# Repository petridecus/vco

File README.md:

6 Voice VCO, designed for Eurorack

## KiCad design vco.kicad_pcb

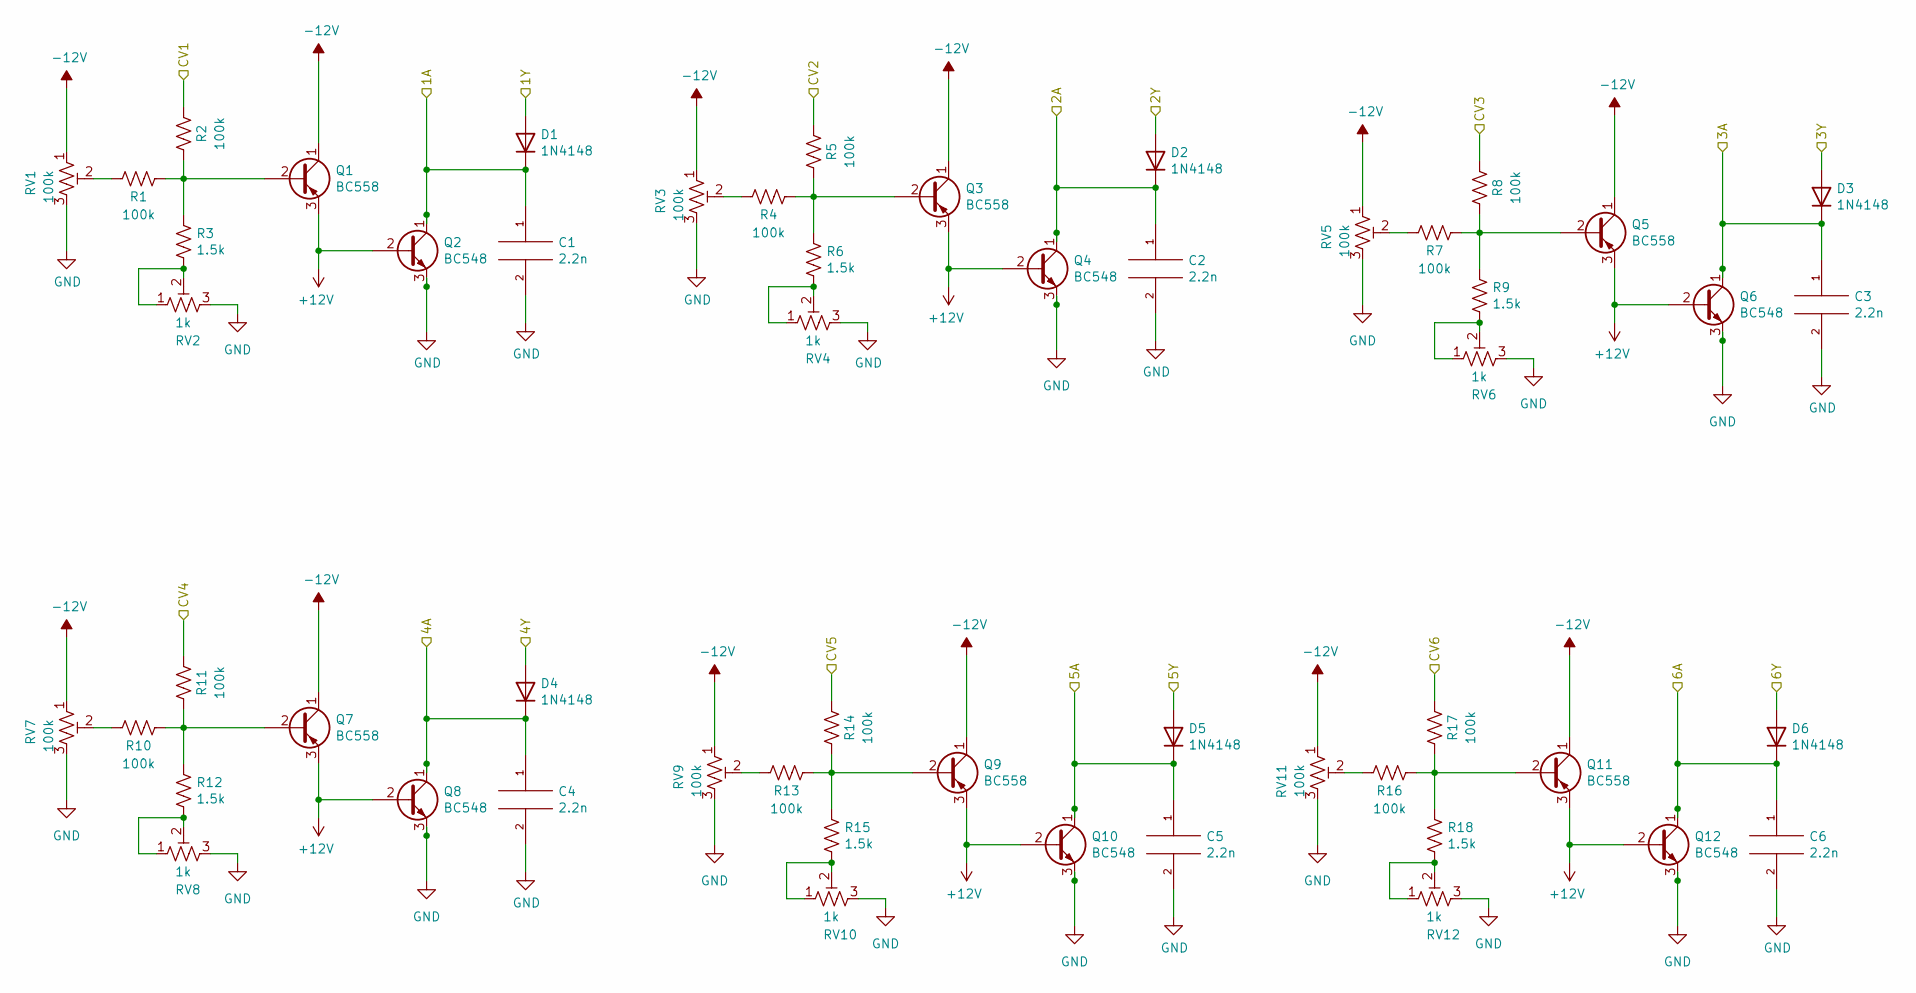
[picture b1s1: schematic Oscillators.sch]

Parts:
C1, C2, C3, C4, C5, C6: 2.2n; C_0603_1608Metric_Pad1.08x0.95mm_HandSolder
D1, D2, D3, D4, D5, D6: 1N4148; D_0603_1608Metric
Q1, Q3, Q5, Q7, Q9, Q11: BC558; SC-59_Handsoldering
Q2, Q4, Q6, Q8, Q10, Q12: BC548; SOT-23_Handsoldering
R1, R2, R4, R5, R7, R8, R10, R11, R13, R14, R16, R17: 100k; R_0603_1608Metric
R3, R6, R9, R12, R15, R18: 1.5k; R_0603_1608Metric
RV1, RV3, RV5, RV7, RV9, RV11: 100k; TRIM_3314J-1-104E
RV2, RV4, RV6, RV8, RV10, RV12: 1k; TRIM_3314J-1-104E

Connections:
+12V: Q1.3 (E), Q2.2 (B), Q3.3 (E), Q4.2 (B), Q5.3 (E), Q6.2 (B), Q7.3 (E), Q8.2 (B), Q9.3 (E), Q10.2 (B), Q11.3 (E), Q12.2 (B); also elsewhere on the board
-12V: Q1.1 (C), Q3.1 (C), Q5.1 (C), Q7.1 (C), Q9.1 (C), Q11.1 (C), RV1.1, RV3.1, RV5.1, RV7.1, RV9.1, RV11.1; also elsewhere on the board
/Sheet614BBE23/1A: C1.1, D1.1 (K), Q2.1 (C); also elsewhere on the board
/Sheet614BBE23/1Y: D1.2 (A); also elsewhere on the board
/Sheet614BBE23/2A: C2.1, D2.1 (K), Q4.1 (C); also elsewhere on the board
/Sheet614BBE23/2Y: D2.2 (A); also elsewhere on the board
/Sheet614BBE23/3A: C3.1, D3.1 (K), Q6.1 (C); also elsewhere on the board
/Sheet614BBE23/3Y: D3.2 (A); also elsewhere on the board
/Sheet614BBE23/4A: C4.1, D4.1 (K), Q8.1 (C); also elsewhere on the board
/Sheet614BBE23/4Y: D4.2 (A); also elsewhere on the board
/Sheet614BBE23/5A: C5.1, D5.1 (K), Q10.1 (C); also elsewhere on the board
/Sheet614BBE23/5Y: D5.2 (A); also elsewhere on the board
/Sheet614BBE23/6A: C6.1, D6.1 (K), Q12.1 (C); also elsewhere on the board
/Sheet614BBE23/6Y: D6.2 (A); also elsewhere on the board
CV1: R2.1; also elsewhere on the board
CV2: R5.1; also elsewhere on the board
CV3: R8.1; also elsewhere on the board
CV4: R11.1; also elsewhere on the board
CV5: R14.1; also elsewhere on the board
CV6: R17.1; also elsewhere on the board
GND: C1.2, C2.2, C3.2, C4.2, C5.2, C6.2, Q2.3 (E), Q4.3 (E), Q6.3 (E), Q8.3 (E), Q10.3 (E), Q12.3 (E), RV1.3, RV2.3, RV3.3, RV4.3, RV5.3, RV6.3, RV7.3, RV8.3, RV9.3, RV10.3, RV11.3, RV12.3; also elsewhere on the board
unnamed: Q1.2 (B), R1.1, R2.2, R3.1
unnamed: Q3.2 (B), R4.1, R5.2, R6.1
unnamed: Q5.2 (B), R7.1, R8.2, R9.1
unnamed: Q7.2 (B), R10.1, R11.2, R12.1
unnamed: Q9.2 (B), R13.1, R14.2, R15.1
unnamed: Q11.2 (B), R16.1, R17.2, R18.1
unnamed: R1.2, RV1.2
unnamed: R3.2, RV2.1, RV2.2
unnamed: R4.2, RV3.2
unnamed: R6.2, RV4.1, RV4.2
unnamed: R7.2, RV5.2
unnamed: R9.2, RV6.1, RV6.2
unnamed: R10.2, RV7.2
unnamed: R12.2, RV8.1, RV8.2
unnamed: R13.2, RV9.2
unnamed: R15.2, RV10.1, RV10.2
unnamed: R16.2, RV11.2
unnamed: R18.2, RV12.1, RV12.2

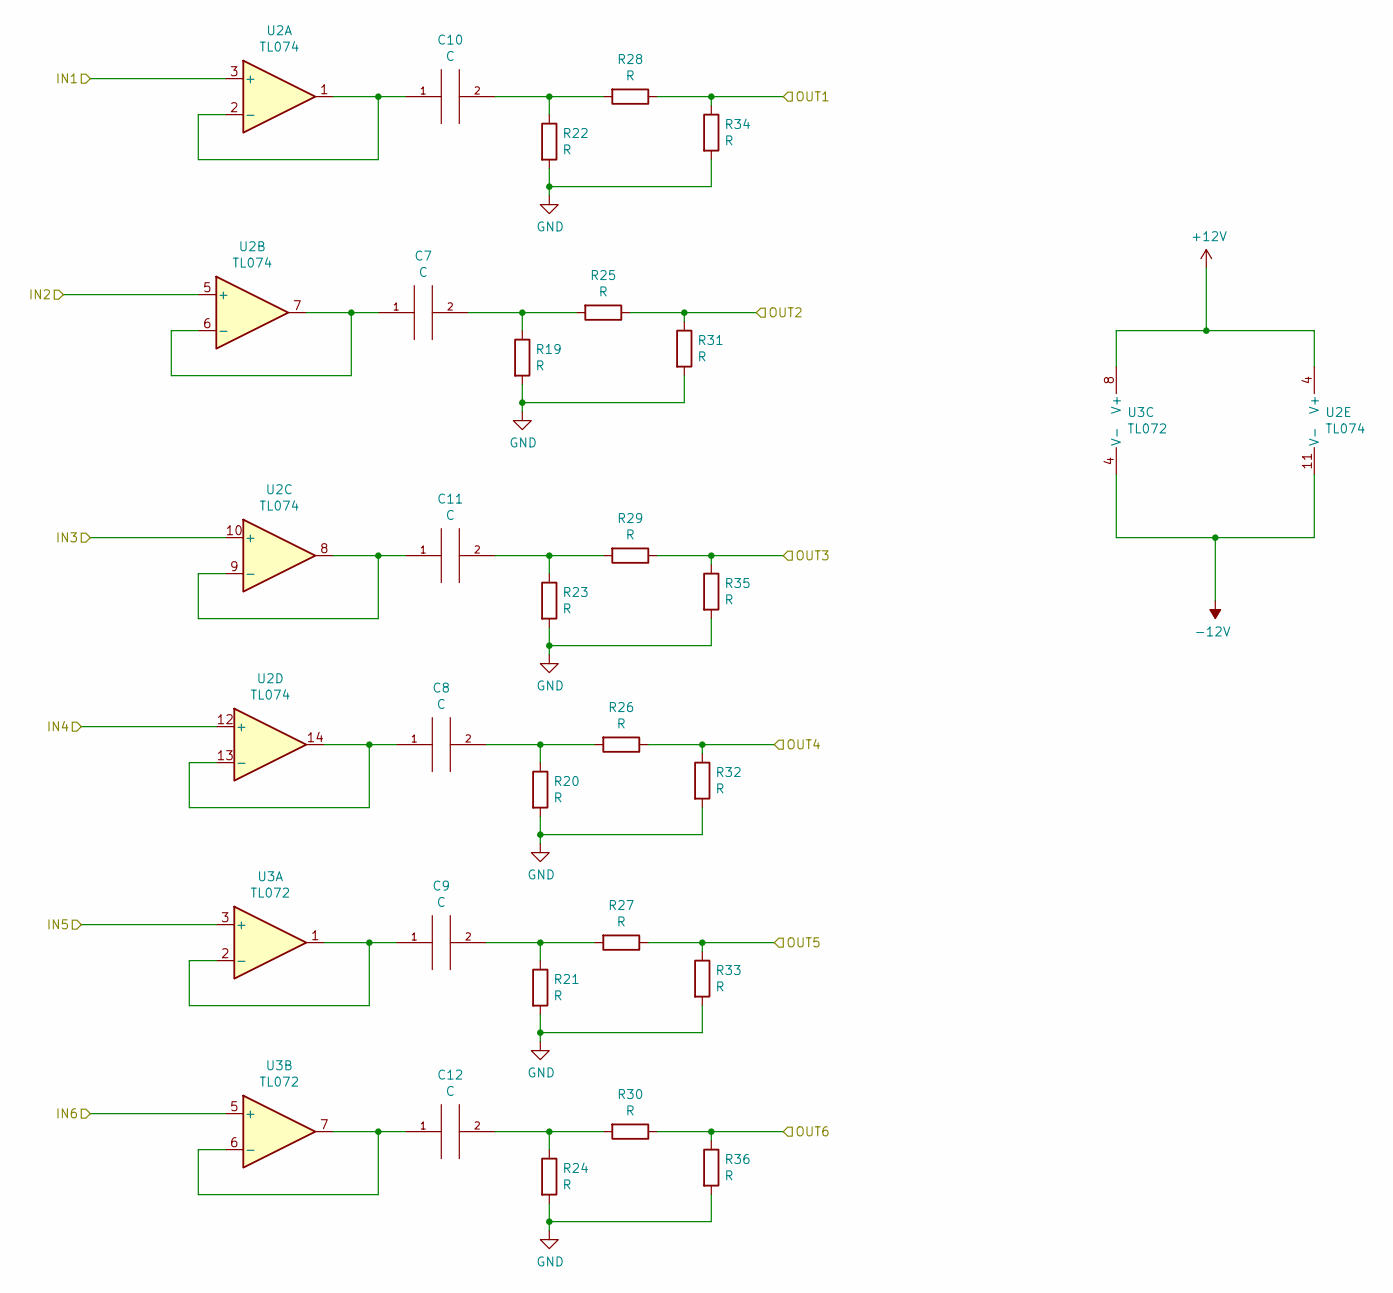
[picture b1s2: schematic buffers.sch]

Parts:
C7, C8, C9, C10, C11, C12: C; C_0603_1608Metric
R19, R20, R21, R22, R23, R24, R25, R26, R27, R28, R29, R30, R31, R32, R33, R34, R35, R36: R; R_0603_1608Metric
U2: TL074; SOIC-14_3.9x8.7mm_P1.27mm
U3: TL072; SOIC-8_3.9x4.9mm_P1.27mm

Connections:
+12V: U2.4 (V+), U3.8 (V+); also elsewhere on the board
-12V: U2.11 (V-), U3.4 (V-); also elsewhere on the board
/Sheet614BBE23/1A: U2.3 (+); also elsewhere on the board
/Sheet614BBE23/2A: U2.5 (+); also elsewhere on the board
/Sheet614BBE23/3A: U2.10 (+); also elsewhere on the board
/Sheet614BBE23/4A: U2.12 (+); also elsewhere on the board
/Sheet614BBE23/5A: U3.3 (+); also elsewhere on the board
/Sheet614BBE23/6A: U3.5 (+); also elsewhere on the board
GND: R19.2, R20.2, R21.2, R22.2, R23.2, R24.2, R31.2, R32.2, R33.2, R34.2, R35.2, R36.2; also elsewhere on the board
unnamed: C7.1, U2.6 (-), U2.7
unnamed: C7.2, R19.1, R25.2
unnamed: C8.1, U2.13 (-), U2.14
unnamed: C8.2, R20.1, R26.2
unnamed: C9.1, U3.1, U3.2 (-)
unnamed: C9.2, R21.1, R27.2
unnamed: C10.1, U2.1, U2.2 (-)
unnamed: C10.2, R22.1, R28.2
unnamed: C11.1, U2.8, U2.9 (-)
unnamed: C11.2, R23.1, R29.2
unnamed: C12.1, U3.6 (-), U3.7
unnamed: C12.2, R24.1, R30.2
OUT1: R28.1, R34.1; also elsewhere on the board
OUT2: R25.1, R31.1; also elsewhere on the board
OUT3: R29.1, R35.1; also elsewhere on the board
OUT4: R26.1, R32.1; also elsewhere on the board
OUT5: R27.1, R33.1; also elsewhere on the board
OUT6: R30.1, R36.1; also elsewhere on the board

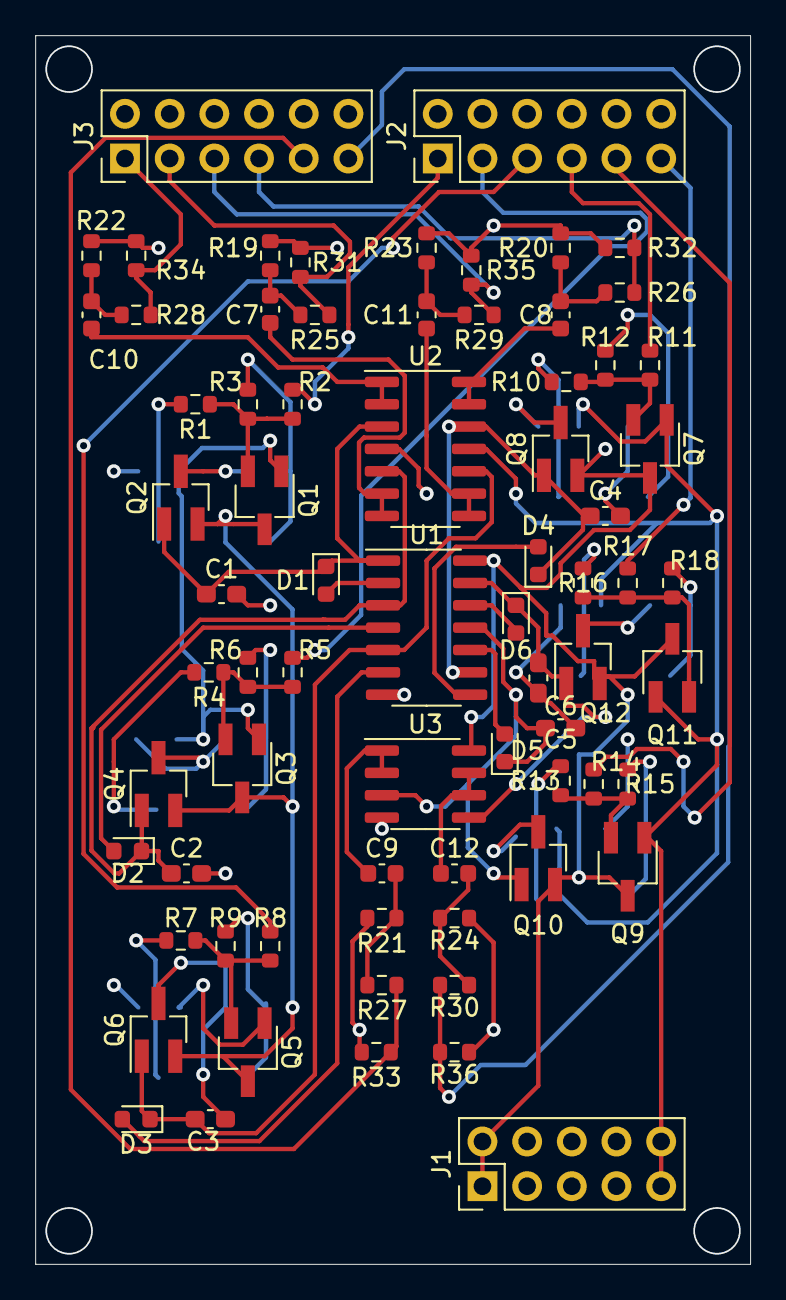
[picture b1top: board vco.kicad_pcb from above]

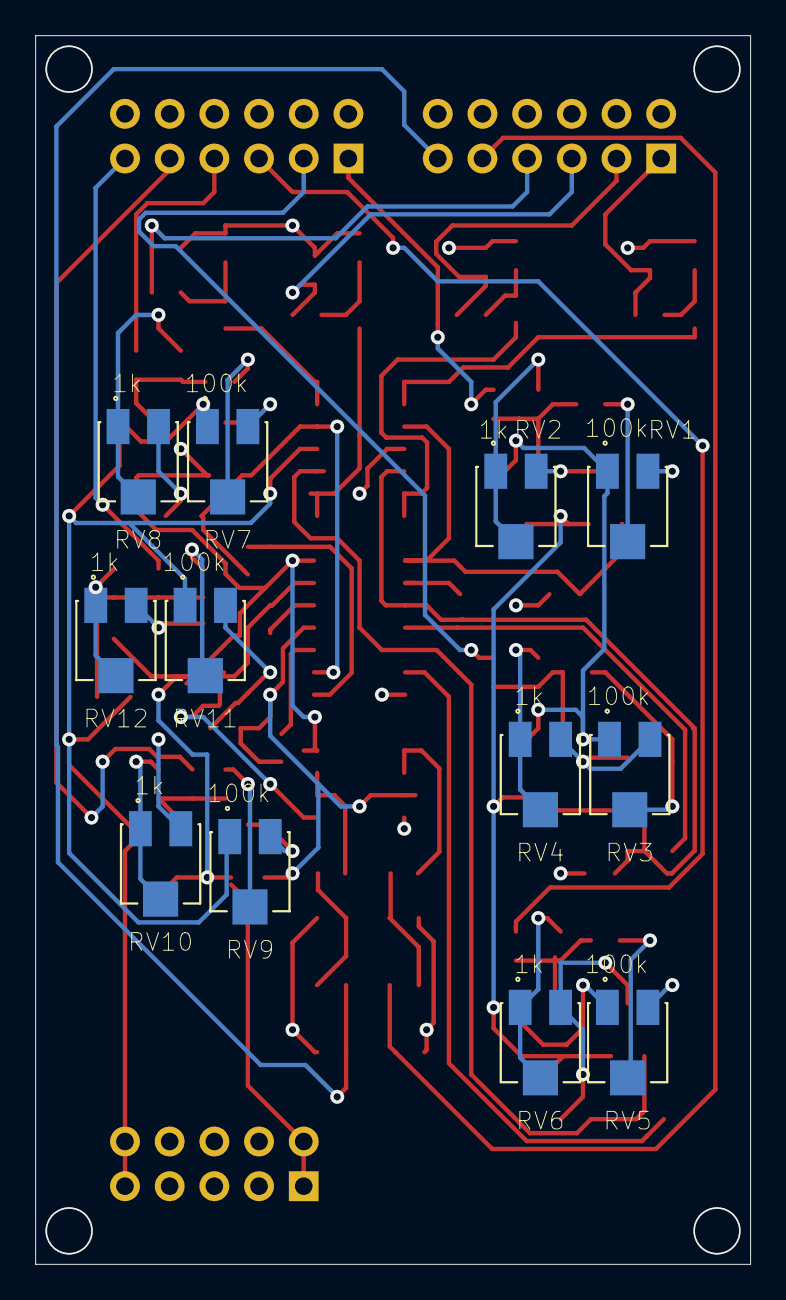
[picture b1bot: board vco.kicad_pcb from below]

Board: 4 copper layers, 40.6 x 69.9 mm, 84 parts (12 on the bottom side), 57 nets.

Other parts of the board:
J1: Conn_02x05_Odd_Even; PinHeader_2x05_P2.54mm_Vertical
J2, J3: Conn_02x06_Odd_Even; PinHeader_2x06_P2.54mm_Vertical
U1: 74HC14D-Q100,118; SOIC-14_3.9x8.7mm_P1.27mm

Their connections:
+12V: J1.1, J1.2, U1.14; also elsewhere on the board
-12V: J1.9, J1.10; also elsewhere on the board
/Sheet614BBE23/1A: U1.1; also elsewhere on the board
/Sheet614BBE23/1Y: U1.2; also elsewhere on the board
/Sheet614BBE23/2A: U1.3; also elsewhere on the board
/Sheet614BBE23/2Y: U1.4; also elsewhere on the board
/Sheet614BBE23/3A: U1.5; also elsewhere on the board
/Sheet614BBE23/3Y: U1.6; also elsewhere on the board
/Sheet614BBE23/4A: U1.9; also elsewhere on the board
/Sheet614BBE23/4Y: U1.8; also elsewhere on the board
/Sheet614BBE23/5A: U1.11; also elsewhere on the board
/Sheet614BBE23/5Y: U1.10; also elsewhere on the board
/Sheet614BBE23/6A: U1.13; also elsewhere on the board
/Sheet614BBE23/6Y: U1.12; also elsewhere on the board
CV1: J2.1; also elsewhere on the board
CV2: J2.3; also elsewhere on the board
CV3: J2.5; also elsewhere on the board
CV4: J2.7; also elsewhere on the board
CV5: J2.9; also elsewhere on the board
CV6: J2.11; also elsewhere on the board
GND: J1.3, J1.4, J1.5, J1.6, J1.7, J1.8, J2.2, J2.4, J2.6, J2.8, J2.10, J2.12, J3.2, J3.4, J3.6, J3.8, J3.10, J3.12, U1.7; also elsewhere on the board
OUT1: J3.1; also elsewhere on the board
OUT2: J3.3; also elsewhere on the board
OUT3: J3.5; also elsewhere on the board
OUT4: J3.7; also elsewhere on the board
OUT5: J3.9; also elsewhere on the board
OUT6: J3.11; also elsewhere on the board

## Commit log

2021-10-21 created repo
2021-11-14 fixed transistor footprints
